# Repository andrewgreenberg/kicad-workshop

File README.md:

# kicad-workshop

3 hours of fun learning KiCAD!

See the [Google Slides](https://docs.google.com/presentation/d/1Ni9xsxwqskmSpj9lokWob5SFJIn1lQJTDu6sBNAD1Mc/edit?usp=sharing) for the outline and notes.

This repo also contains:

- Example .gitignore file
- DRC files for 2 and 4 layer OSH Park boards
- Workshop CAD files

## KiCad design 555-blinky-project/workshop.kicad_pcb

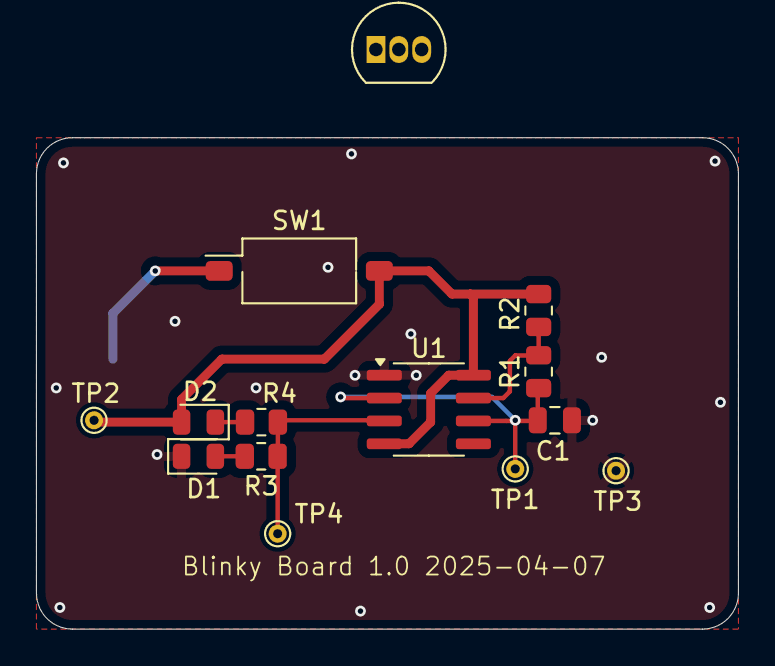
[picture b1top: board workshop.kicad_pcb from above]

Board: 2 copper layers, 39.0 x 27.3 mm, 15 parts (1 on the bottom side), 8 nets.

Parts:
BT2: CR2023 battery holder; BatteryHolder_Keystone_1060_1x2032
C1: 300n; C_0805_2012Metric
D1, D2: RED; LED_0805_2012Metric
Q1: BIGMOSFET; TO-92_Inline
R1, R2: 10k; R_0805_2012Metric
R3, R4: 330; R_0805_2012Metric
SW1: SW_SPST; SW_DIP_SPSTx01_Slide_Omron_A6S-110x_W8.9mm_P2.54mm
TP1, TP2, TP3, TP4: TestPoint; TestPoint_THTPad_D1.0mm_Drill0.5mm
U1: ICM7555xB; SOIC-8_3.9x4.9mm_P1.27mm

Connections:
+BATT: D2.2 (A), R2.1, SW1.2 (B), TP2.1, U1.4 (R), U1.8 (VCC)
GND: BT2.2 (-), C1.2, D1.1 (K), TP3.1, U1.1 (GND)
unnamed: BT2.1 (+), SW1.1 (A)
unnamed: D1.2 (A), R3.2
unnamed: D2.1 (K), R4.1
unnamed: R1.1, R2.2, U1.7 (DIS)
unnamed: R3.1, R4.2, TP4.1, U1.3 (Q)
unnamed: C1.1, R1.2, TP1.1, U1.2 (TR), U1.6 (THR)

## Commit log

2021-11-26 Checking commit writes.
2021-11-26 Added KiCAD 5.99 file as a DRC template for OSH Park 2 layer process.
2025-04-08 Updated for 3 hour KiCAD 9.0.1 workshop!
2025-04-08 Updated 2 and 4 layer templates to KiCAD 9
2025-04-08 Better project folder name
